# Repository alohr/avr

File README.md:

# avr

My AVR sandbox. Experimental stuff for Atmel microcontrollers.

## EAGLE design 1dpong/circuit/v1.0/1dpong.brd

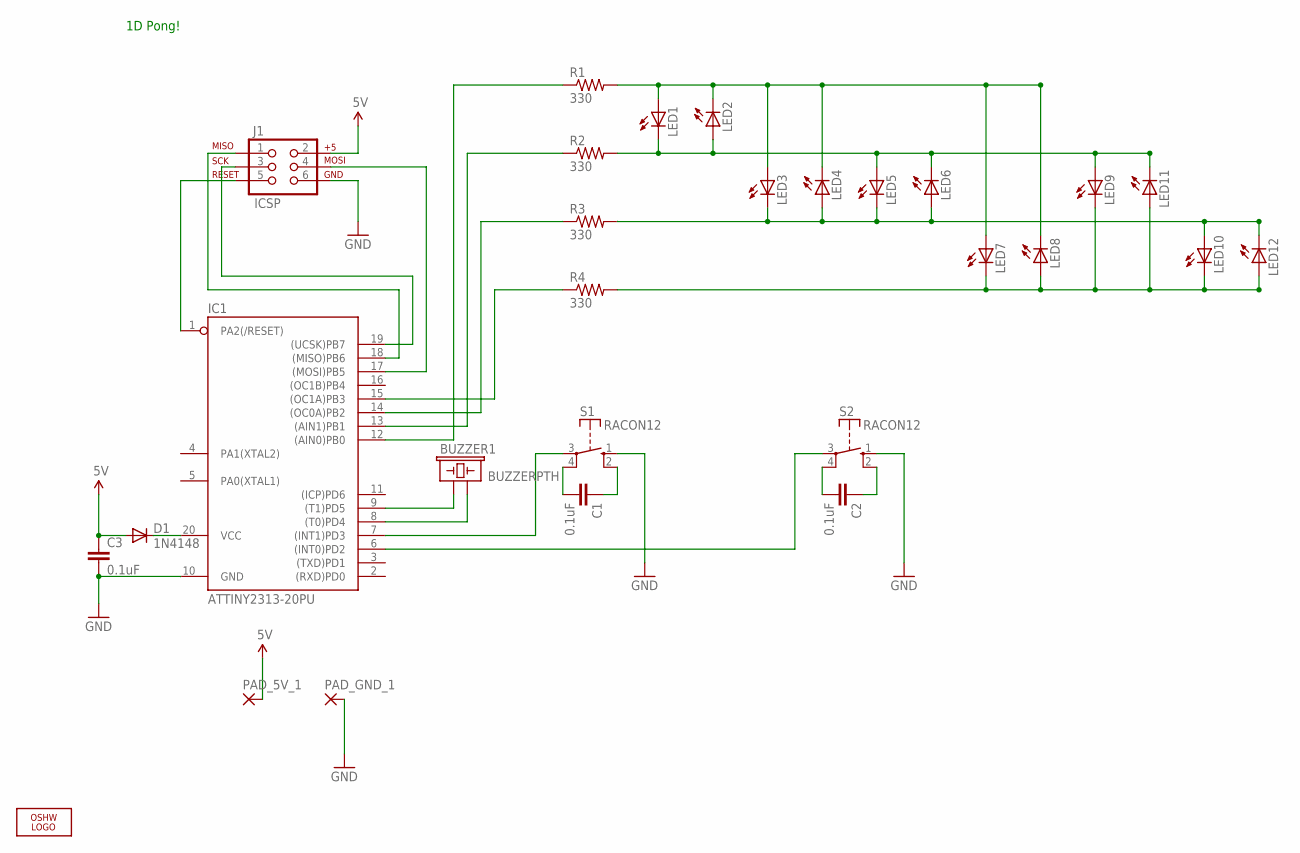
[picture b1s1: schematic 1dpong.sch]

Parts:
BUZZER1: BUZZERPTH; BUZZER-12MM
C1, C2, C3: 0.1uF; CAP-PTH-SMALL
D1: 1N4148; DIODE-1N4148
IC1: ATTINY2313-20PU; DIL20
J1: ICSP; 2X3
LED1, LED2, LED3, LED4, LED5, LED6, LED7, LED8, LED9, LED10, LED11, LED12: LED5MM
LOGO1: OSHW_LOGO_FILLX0150-NT; OSHW_FILLX150_NOTEXT
PAD_5V_1: WIREPAD1,6/0,9; 1,6/0,9
PAD_GND_1: WIREPAD1,6/0,9; 1,6/0,9
R1, R2, R3, R4: 330; AXIAL-0.4
S1, S2: RACON12

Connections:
5V: C3.1, D1.A, J1.2, PAD_5V_1.1
GND: C3.2, IC1.10 (GND), J1.6, PAD_GND_1.1, S1.1 (S), S2.1 (S)
unnamed: IC1.1 (PA2(/RESET)), J1.5
unnamed: IC1.19 ((UCSK)PB7), J1.3
unnamed: LED1.A, LED2.K (C), LED3.A, LED4.K (C), LED7.A, LED8.K (C), R1.P$2 (2)
unnamed: LED1.K (C), LED2.A, LED5.A, LED6.K (C), LED9.A, LED11.K (C), R2.P$2 (2)
unnamed: LED3.K (C), LED4.A, LED5.K (C), LED6.A, LED10.A, LED12.K (C), R3.P$2 (2)
unnamed: BUZZER1.+ (1), IC1.9 ((T1)PD5)
unnamed: LED7.K (C), LED8.A, LED9.K (C), LED10.K (C), LED11.A, LED12.A, R4.P$2 (2)
unnamed: BUZZER1.- (2), IC1.8 ((T0)PD4)
unnamed: IC1.18 ((MISO)PB6), J1.1
unnamed: IC1.15 ((OC1A)PB3), R4.P$1 (1)
unnamed: D1.C, IC1.20 (VCC)
unnamed: IC1.17 ((MOSI)PB5), J1.4
unnamed: IC1.12 ((AIN0)PB0), R1.P$1 (1)
unnamed: IC1.13 ((AIN1)PB1), R2.P$1 (1)
unnamed: IC1.14 ((OC0A)PB2), R3.P$1 (1)
unnamed: IC1.7 ((INT1)PD3), S1.3
unnamed: IC1.6 ((INT0)PD2), S2.3
unnamed: C1.2, S1.4
unnamed: C1.1, S1.2 (S)
unnamed: C2.2, S2.4
unnamed: C2.1, S2.2 (S)

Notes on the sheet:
1D Pong!

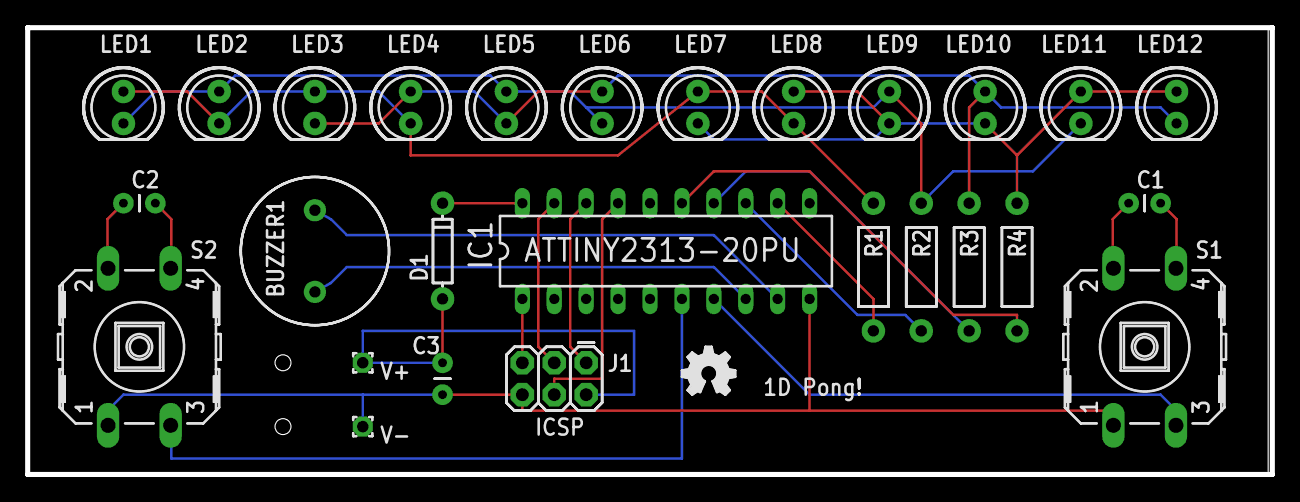
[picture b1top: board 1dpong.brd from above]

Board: 2 copper layers, 99.1 x 35.6 mm, 28 parts (0 on the bottom side), 23 nets.

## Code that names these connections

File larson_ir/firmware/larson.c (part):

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		    {
			uint8_t i = 0;
			for (i = 0; i < 5; i++) {
			    PORTB |= _BV(PB5);
			    _delay_ms(100);
			    PORTB &= ~(_BV(PB5));
			}
		    }

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
		portd = PORTD & 0x83;
		if (LED0 > j)
		    PORTD = portd | _BV(PD2);
		else
		    PORTD = portd & ~(_BV(PD2));

		if (LED1 > j)
		    PORTD = portd | _BV(PD3);
		else
		    PORTD = portd & ~(_BV(PD3));

		if (LED2 > j)
		    PORTD = portd | _BV(PD4);
		else
		    PORTD = portd & ~(_BV(PD4));

		if (LED3 > j)
		    PORTD = portd | _BV(PD5);
		else
		    PORTD = portd & ~(_BV(PD5));

		if (LED4 > j)
		    PORTD = portd | _BV(PD6);
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
		portb = PORTB & 0xf0;
		if (LED5 > j) {
		    PORTB = portb | _BV(PB0);
		    PORTD = portd;
		} else {
		    PORTB = portb;
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		}

		if (LED6 > j)
		    PORTB = portb | _BV(PB1);
		else
		    PORTB = portb & ~(_BV(PB1));

		if (LED7 > j)
		    PORTB = portb | _BV(PB2);
		else
		    PORTB = portb & ~(_BV(PB2));

		if (LED8 > j)
		    PORTB = portb | _BV(PB3);
		else
		    PORTB = portb & ~(_BV(PB3));

		j++;
		asm("nop");	 // Delay to make up time difference versus branch.
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	    while (j < 70) {
		pt = 0;
		if (LED0 > j)
		    pt = _BV(PD2);
		if (LED1 > j)
		    pt |= _BV(PD3);
		if (LED2 > j)
		    pt |= _BV(PD4);
		if (LED3 > j)
		    pt |= _BV(PD5);
		if (LED4 > j)
		    pt |= _BV(PD6);

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
		pt = 0;
		if (LED5 > j)
		    pt |= _BV(PB0);
		if (LED6 > j)
		    pt |= _BV(PB1);
		if (LED7 > j)
		    pt |= _BV(PB2);
		if (LED8 > j) 
		    pt |= _BV(PB3);
		
		PORTB = (PORTB & 0xe0) | pt;
		shortdelay();
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
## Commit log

2012-04-24 added README
2012-04-24 use PB5 for the indicator led
2012-04-24 added README.md
2012-04-25 use timer1, run at 16 Mhz
2012-04-26 added larrson_ir
2012-04-26 use timer0
2012-04-28 added .gitignore
2012-04-28 added ir receive code
2012-04-28 blinkflag
2012-04-29 test irrecv with rc5 remote control
2012-04-29 added timer and auto-increment
2012-05-05 use less memory, implement running light
2012-05-05 allow running light to change direction
2012-05-06 change default fuses to use internal oscillator
2012-06-09 moved directory
2012-06-09 updated reference to fuses.mk
2012-06-09 removed README
2012-09-02 added ftcontrol
2012-09-12 removed REPEAT from decodeRC5
2012-09-12 reduce memory usage for rc5 only
2012-11-03 added lighthouse
2012-12-22 added 1dpong
2013-03-03 added sound
2013-03-03 added 1dpong-bb
2013-03-09 added ftcontrol2
2013-03-09 added atmega8 ext flags
2013-03-09 different powerdown durations
2013-03-09 cleanup
2013-03-17 added esmblink
2013-03-17 added esmanalog
2013-04-06 rearrange 1dpong
2013-04-06 shrink 1dpong-oshpark.png
2013-05-02 added board and eagle project file
2013-05-19 added 2nd motor
2014-11-30 added delaymachine
2015-11-27 timer1
2015-11-27 removed main.c
2015-11-28 fixed attiny85 8 mhz
2015-11-28 removed local fuses.mk
2015-11-28 moved files
2015-11-28 use lib fuses.mk
2015-12-23 fixed typo
2015-12-23 return raw value
2015-12-23 added ping
2015-12-23 added blink test programs
2015-12-23 added buttontest
2015-12-23 added buzzertest
2015-12-23 added servotester

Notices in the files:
larson_ir/firmware/larson.c:
Copyright 2011 Windell H. Oskay
Distributed under the terms of the GNU General Public License, please see below.
parts and their libraries:
SparkFun-LED: Licensing: CC v3.0 Share-Alike You are welcome to use this library for commercial purposes.
